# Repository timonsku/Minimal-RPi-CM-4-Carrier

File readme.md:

Some photos can be found here: https://hackaday.io/project/175832-minimal-raspberry-pi-cm-4-carrier

Why
------
The goal was to show how little you have to do to do a fairly feature rich carrier board for the Compute Module 4. Also to demonstrate that you don't have to be scared by high-speed signals like HDMI and that they can still work fine in very bad conditions like a single layer PCB like this one without a reference plane underneath.

Please only use this as a starting point if at all and take a look at the open reference design by the Pi foundation for a more in-depth carrier design. This design skips several saftey features like load switches on the USB and HDMI, most of the time that's fine but you should make sure that you really don't care about that.

Please do not see this as best pracitize what so ever when it comes to routing. This PCB was made for milling a CNC and thus a lot of very bad trade offs were made that you can completely avoid by using a normal PCB fab.

Also do please attempt to do some impedance matching. An online calculator to get the correct trace width is already an ok approximation for most hobby use cases. JLC f.e. has their own calculator tuned to their specific stackups: https://cart.jlcpcb.com/impedanceCalculation

4 Layer PCBs are to be had for 5$ and less now a days so I really suggest using 4 layers, no matter what you plan.

The PCB is done in Eagle, if you use KiCad I suggest just using the schematic as a starting point and use the official Dev Board carrier design as your basis as that already comes as a KiCad design.

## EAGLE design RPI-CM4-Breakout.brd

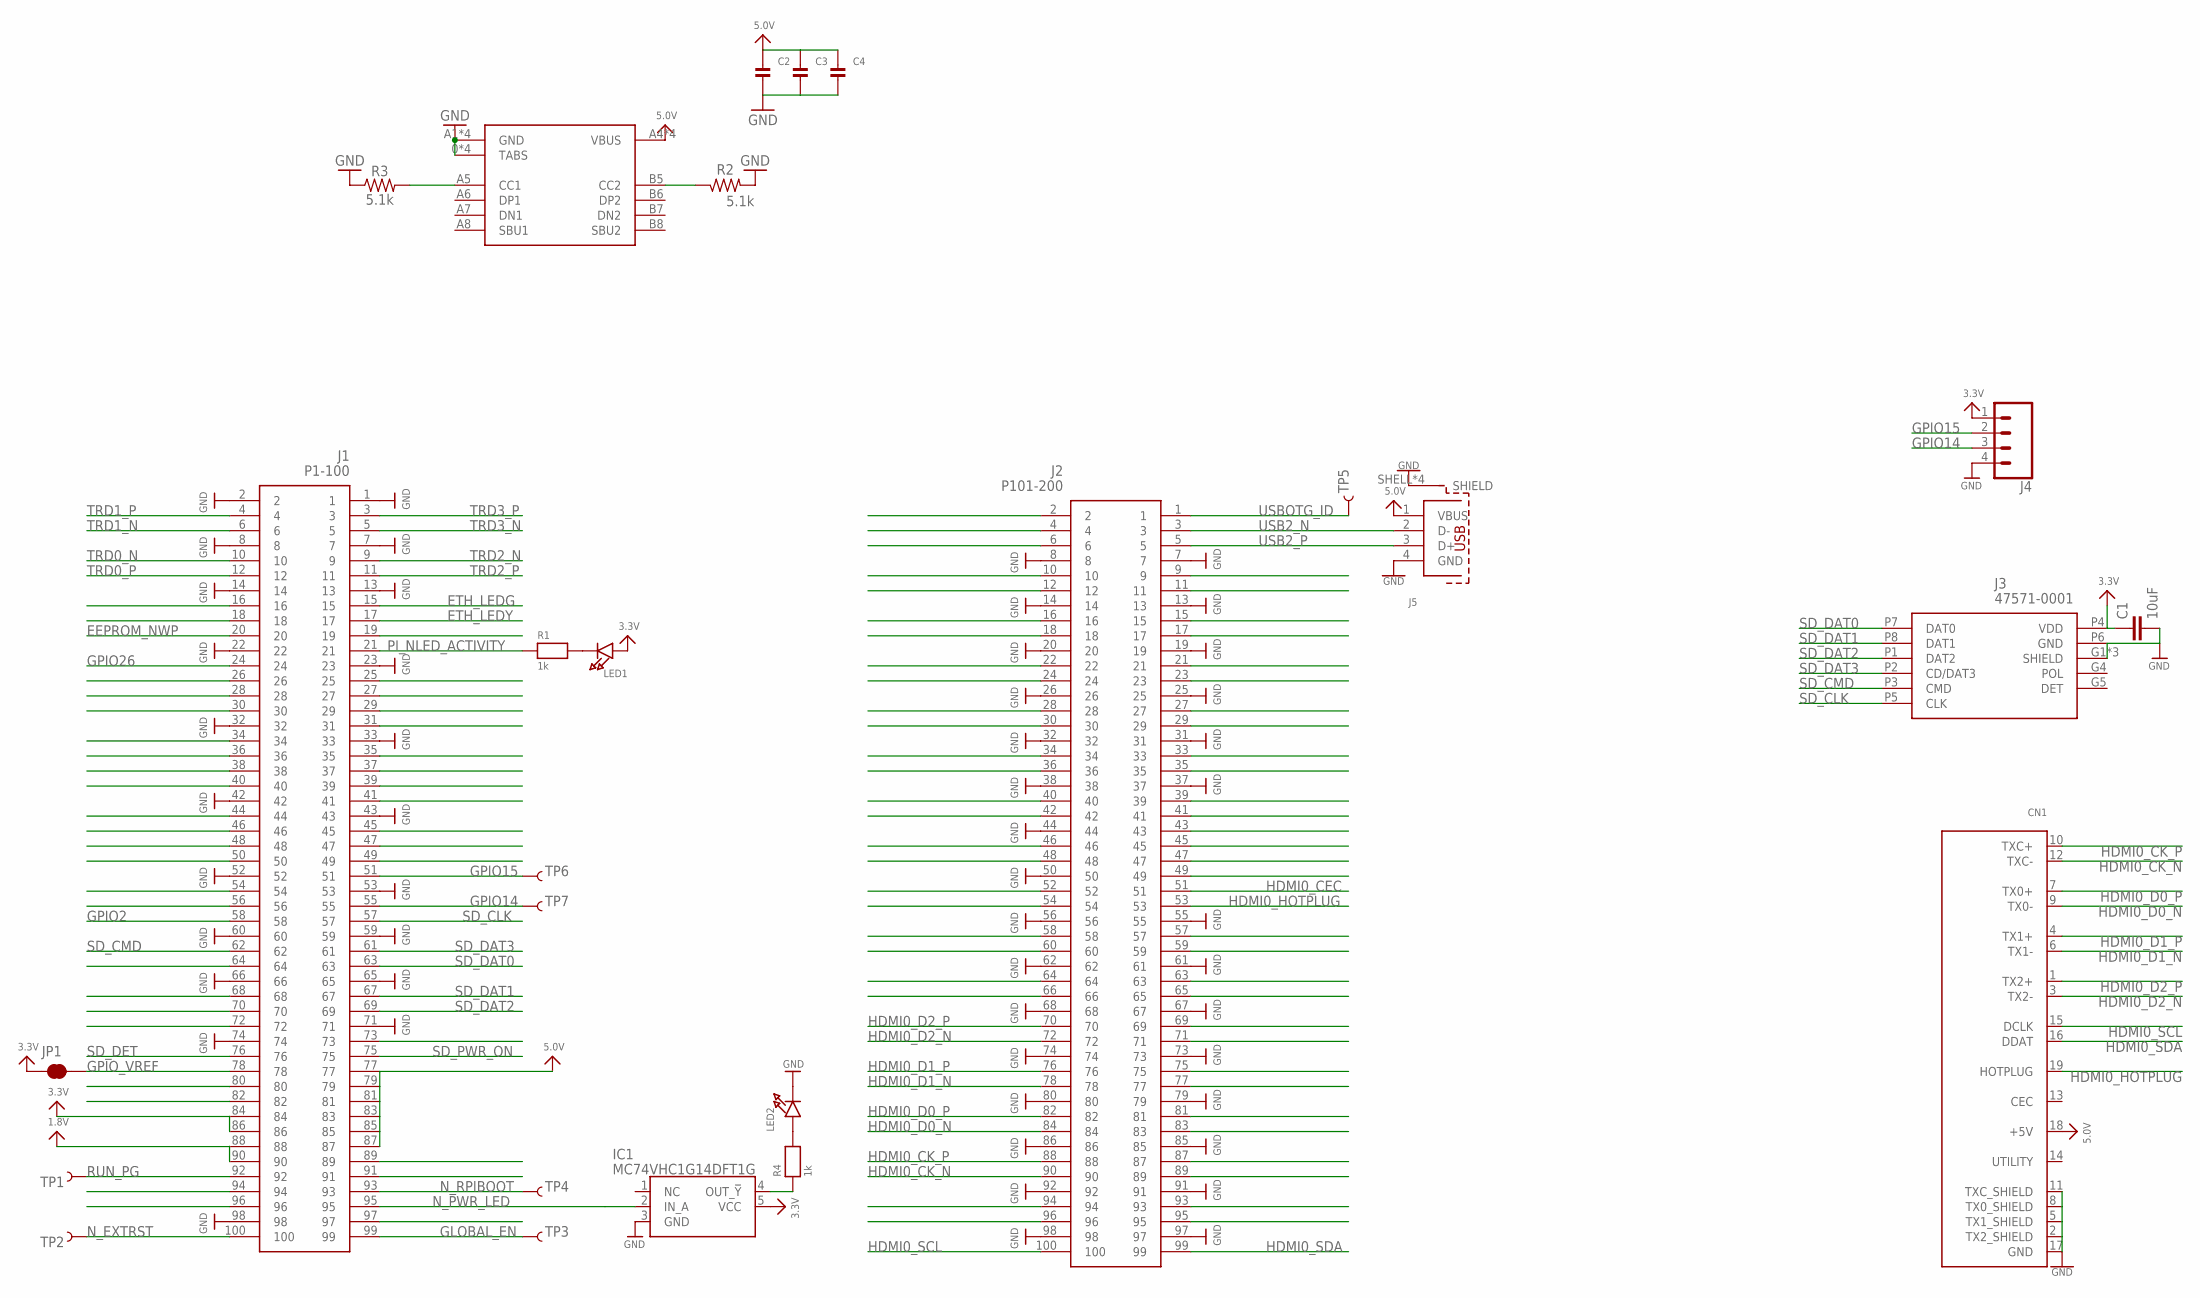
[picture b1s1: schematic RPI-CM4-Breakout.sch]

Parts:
C1: 10uF; 0603
C2, C3, C4: CAP_CERAMIC0402; 0402
CN1: HDMI_MOLEX_47151-0001
IC1: MC74VHC1G14DFT1G; SOT65P210X110-5N
J1: P1-100; DF40C100DS04V51
J2: P101-200; DF40C100DS04V51
J3: 47571-0001
J4: CONN_04SMD_RA_FEMALE; 1X04_SMD_RA_FEMALE
J5: 629104190121
JP1: JUMPER-SMT_2_NC_TRACE_NO-SILK; SMT-JUMPER_2_NC_TRACE_NO-SILK
LED1, LED2: LED0603; CHIPLED_0603
R1, R4: 1k; _0402MP
R2, R3: 5.1k; 0603
TP1, TP2, TP3, TP4, TP5, TP6, TP7: TEST-POINT3X5; PAD.03X.05
U$59: TYPE-C-31-M-12; USB-TYPE-C_16PIN-MALE-TYPE-C-31-M-12

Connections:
1.8V: J1.88, J1.90
3.3V: C1.1, IC1.5 (VCC), J1.84, J1.86, J3.P4 (VDD), J4.1, JP1.1, LED1.A
5.0V: C2.1, C3.1, C4.1, CN1.18 (+5V), J1.77, J1.79, J1.81, J1.83, J1.85, J1.87, J5.1 (VBUS), U$59.A4 (VBUS), U$59.A9 (VBUS), U$59.B4 (VBUS), U$59.B9 (VBUS)
A0/CC2: R3.2, U$59.A5 (CC1)
A3/CC1: R2.1, U$59.B5 (CC2)
EEPROM_NWP: J1.20
ETH_LEDG: J1.15
ETH_LEDY: J1.17
GLOBAL_EN: J1.99, TP3.P$1
GND: C1.2, C2.2, C3.2, C4.2, CN1.2 (TX2_SHIELD), CN1.5 (TX1_SHIELD), CN1.8 (TX0_SHIELD), CN1.11 (TXC_SHIELD), CN1.17 (GND), CN1.P$1 (GND), CN1.P$2 (GND), CN1.P$3 (GND), CN1.P$4 (GND), IC1.3 (GND), J1.1, J1.2, J1.7, J1.8, J1.13, J1.14, J1.22, J1.23, J1.32, J1.33, J1.42, J1.43, J1.52, J1.53, J1.59, J1.60, J1.65, J1.66, J1.71, J1.74, J1.98, J2.7, J2.8, J2.13, J2.14, J2.19, J2.20, J2.25, J2.26, J2.31, J2.32, J2.37, J2.38, J2.44, J2.50, J2.55, J2.56, J2.61, J2.62, J2.67, J2.68, J2.73, J2.74, J2.79, J2.80, J2.85, J2.86, J2.91, J2.92, J2.97, J2.98, J3.G1 (SHIELD), J3.G2 (SHIELD), J3.G3 (SHIELD), J3.P6 (GND), J4.4, J5.4 (GND), J5.SHELL (SHIELD), J5.SHELL1 (SHIELD), J5.SHELL2 (SHIELD), J5.SHELL3 (SHIELD), LED2.C, R2.2, R3.1, U$59.0 (TABS), U$59.0-1 (TABS), U$59.0-2 (TABS), U$59.0-3 (TABS), U$59.A1 (GND), U$59.A12 (GND), U$59.B1 (GND), U$59.B12 (GND)
GPIO2: J1.58
GPIO14: J1.55, J4.3, TP7.P$1
GPIO15: J1.51, J4.2, TP6.P$1
GPIO26: J1.24
GPIO_VREF: J1.78, JP1.2
HDMI0_CEC: J2.51
HDMI0_CK_N: CN1.12 (TXC-), J2.90
HDMI0_CK_P: CN1.10 (TXC+), J2.88
HDMI0_D0_N: CN1.9 (TX0-), J2.84
HDMI0_D0_P: CN1.7 (TX0+), J2.82
HDMI0_D1_N: CN1.6 (TX1-), J2.78
HDMI0_D1_P: CN1.4 (TX1+), J2.76
HDMI0_D2_N: CN1.3 (TX2-), J2.72
HDMI0_D2_P: CN1.1 (TX2+), J2.70
HDMI0_HOTPLUG: CN1.19 (HOTPLUG), J2.53
HDMI0_SCL: CN1.15 (DCLK), J2.100
HDMI0_SDA: CN1.16 (DDAT), J2.99
unnamed: LED1.C, R1.2
unnamed: IC1.4 (OUT_!Y), R4.1
unnamed: LED2.A, R4.2
N_EXTRST: J1.100, TP2.P$1
N_PWR_LED: IC1.2 (IN_A), J1.95
N_RPIBOOT: J1.93, TP4.P$1
PI_NLED_ACTIVITY: J1.21, R1.1
RUN_PG: J1.92, TP1.P$1
SD_CLK: J1.57, J3.P5 (CLK)
SD_CMD: J1.62, J3.P3 (CMD)
SD_DAT0: J1.63, J3.P7 (DAT0)
SD_DAT1: J1.67, J3.P8 (DAT1)
SD_DAT2: J1.69, J3.P1 (DAT2)
SD_DAT3: J1.61, J3.P2 (CD/DAT3)
SD_DET: J1.76
SD_PWR_ON: J1.75
TRD0_N: J1.10
TRD0_P: J1.12
TRD1_N: J1.6
TRD1_P: J1.4
TRD2_N: J1.9
TRD2_P: J1.11
TRD3_N: J1.5
TRD3_P: J1.3
USB2_N: J2.3, J5.2 (D-)
USB2_P: J2.5, J5.3 (D+)
USBOTG_ID: J2.1, TP5.P$1

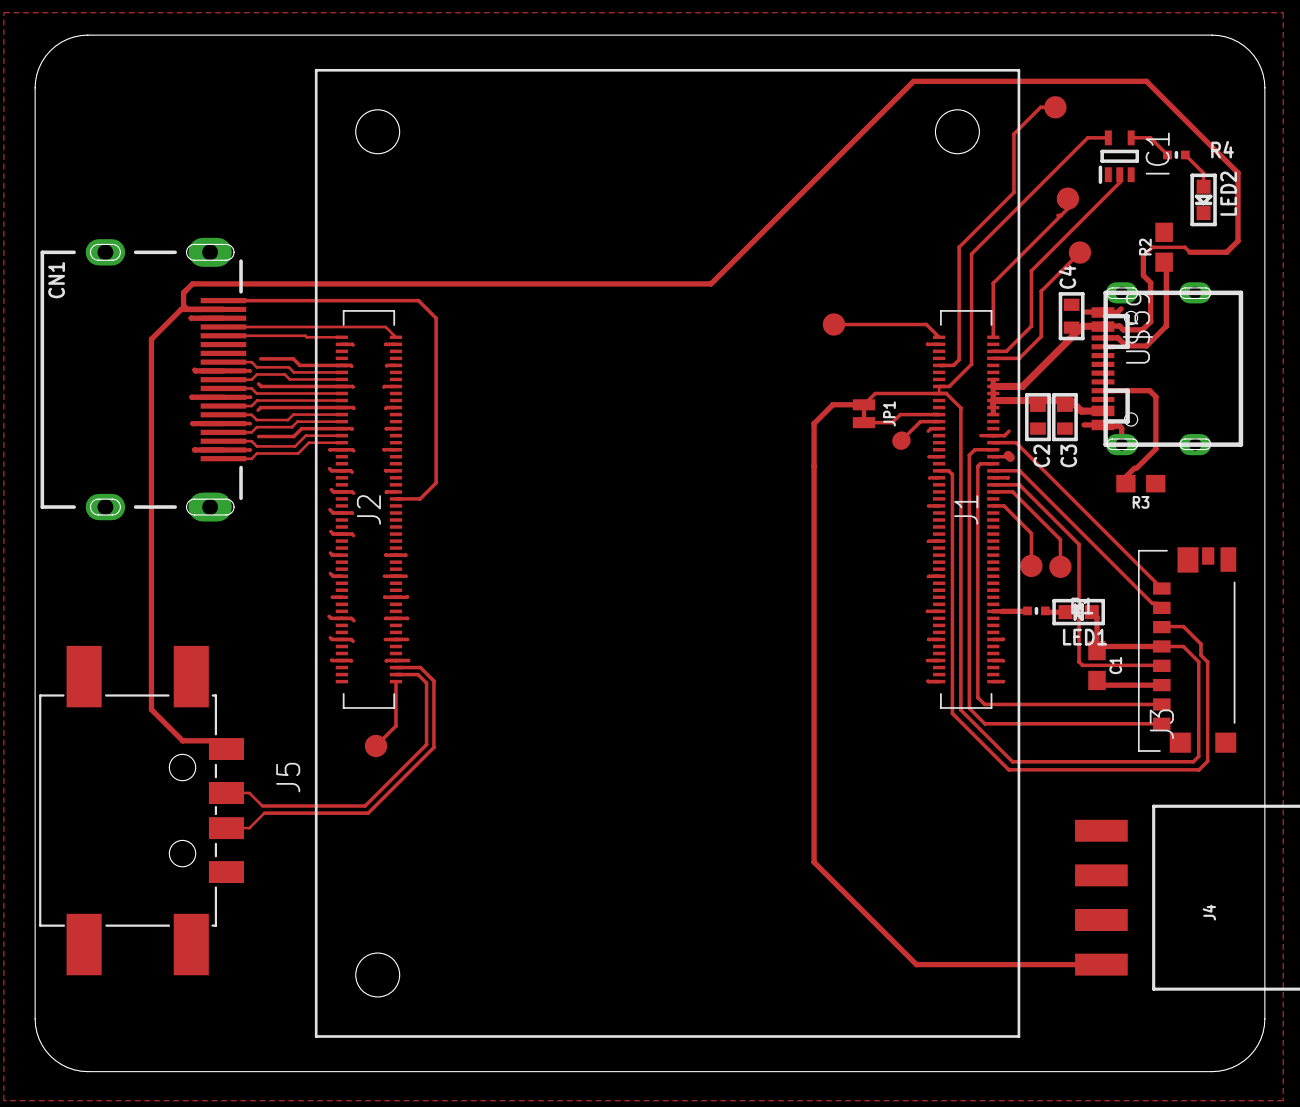
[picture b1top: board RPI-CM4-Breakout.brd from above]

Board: 2 copper layers, 70.0 x 59.0 mm, 26 parts (0 on the bottom side), 38 nets.

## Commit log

2020-11-12 Initial single layer version
2020-11-21 Removed misleading pull-down on GLOBAL_EN

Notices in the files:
parts and their libraries:
SparkFun-Capacitors: Licensing: Creative Commons ShareAlike 4.0 International - https://creativecommons.org/licenses/by-sa/4.0
microbuilder: This work is placed in the public domain, and may be freely used for commercial and non-commercial work with the following conditions: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
